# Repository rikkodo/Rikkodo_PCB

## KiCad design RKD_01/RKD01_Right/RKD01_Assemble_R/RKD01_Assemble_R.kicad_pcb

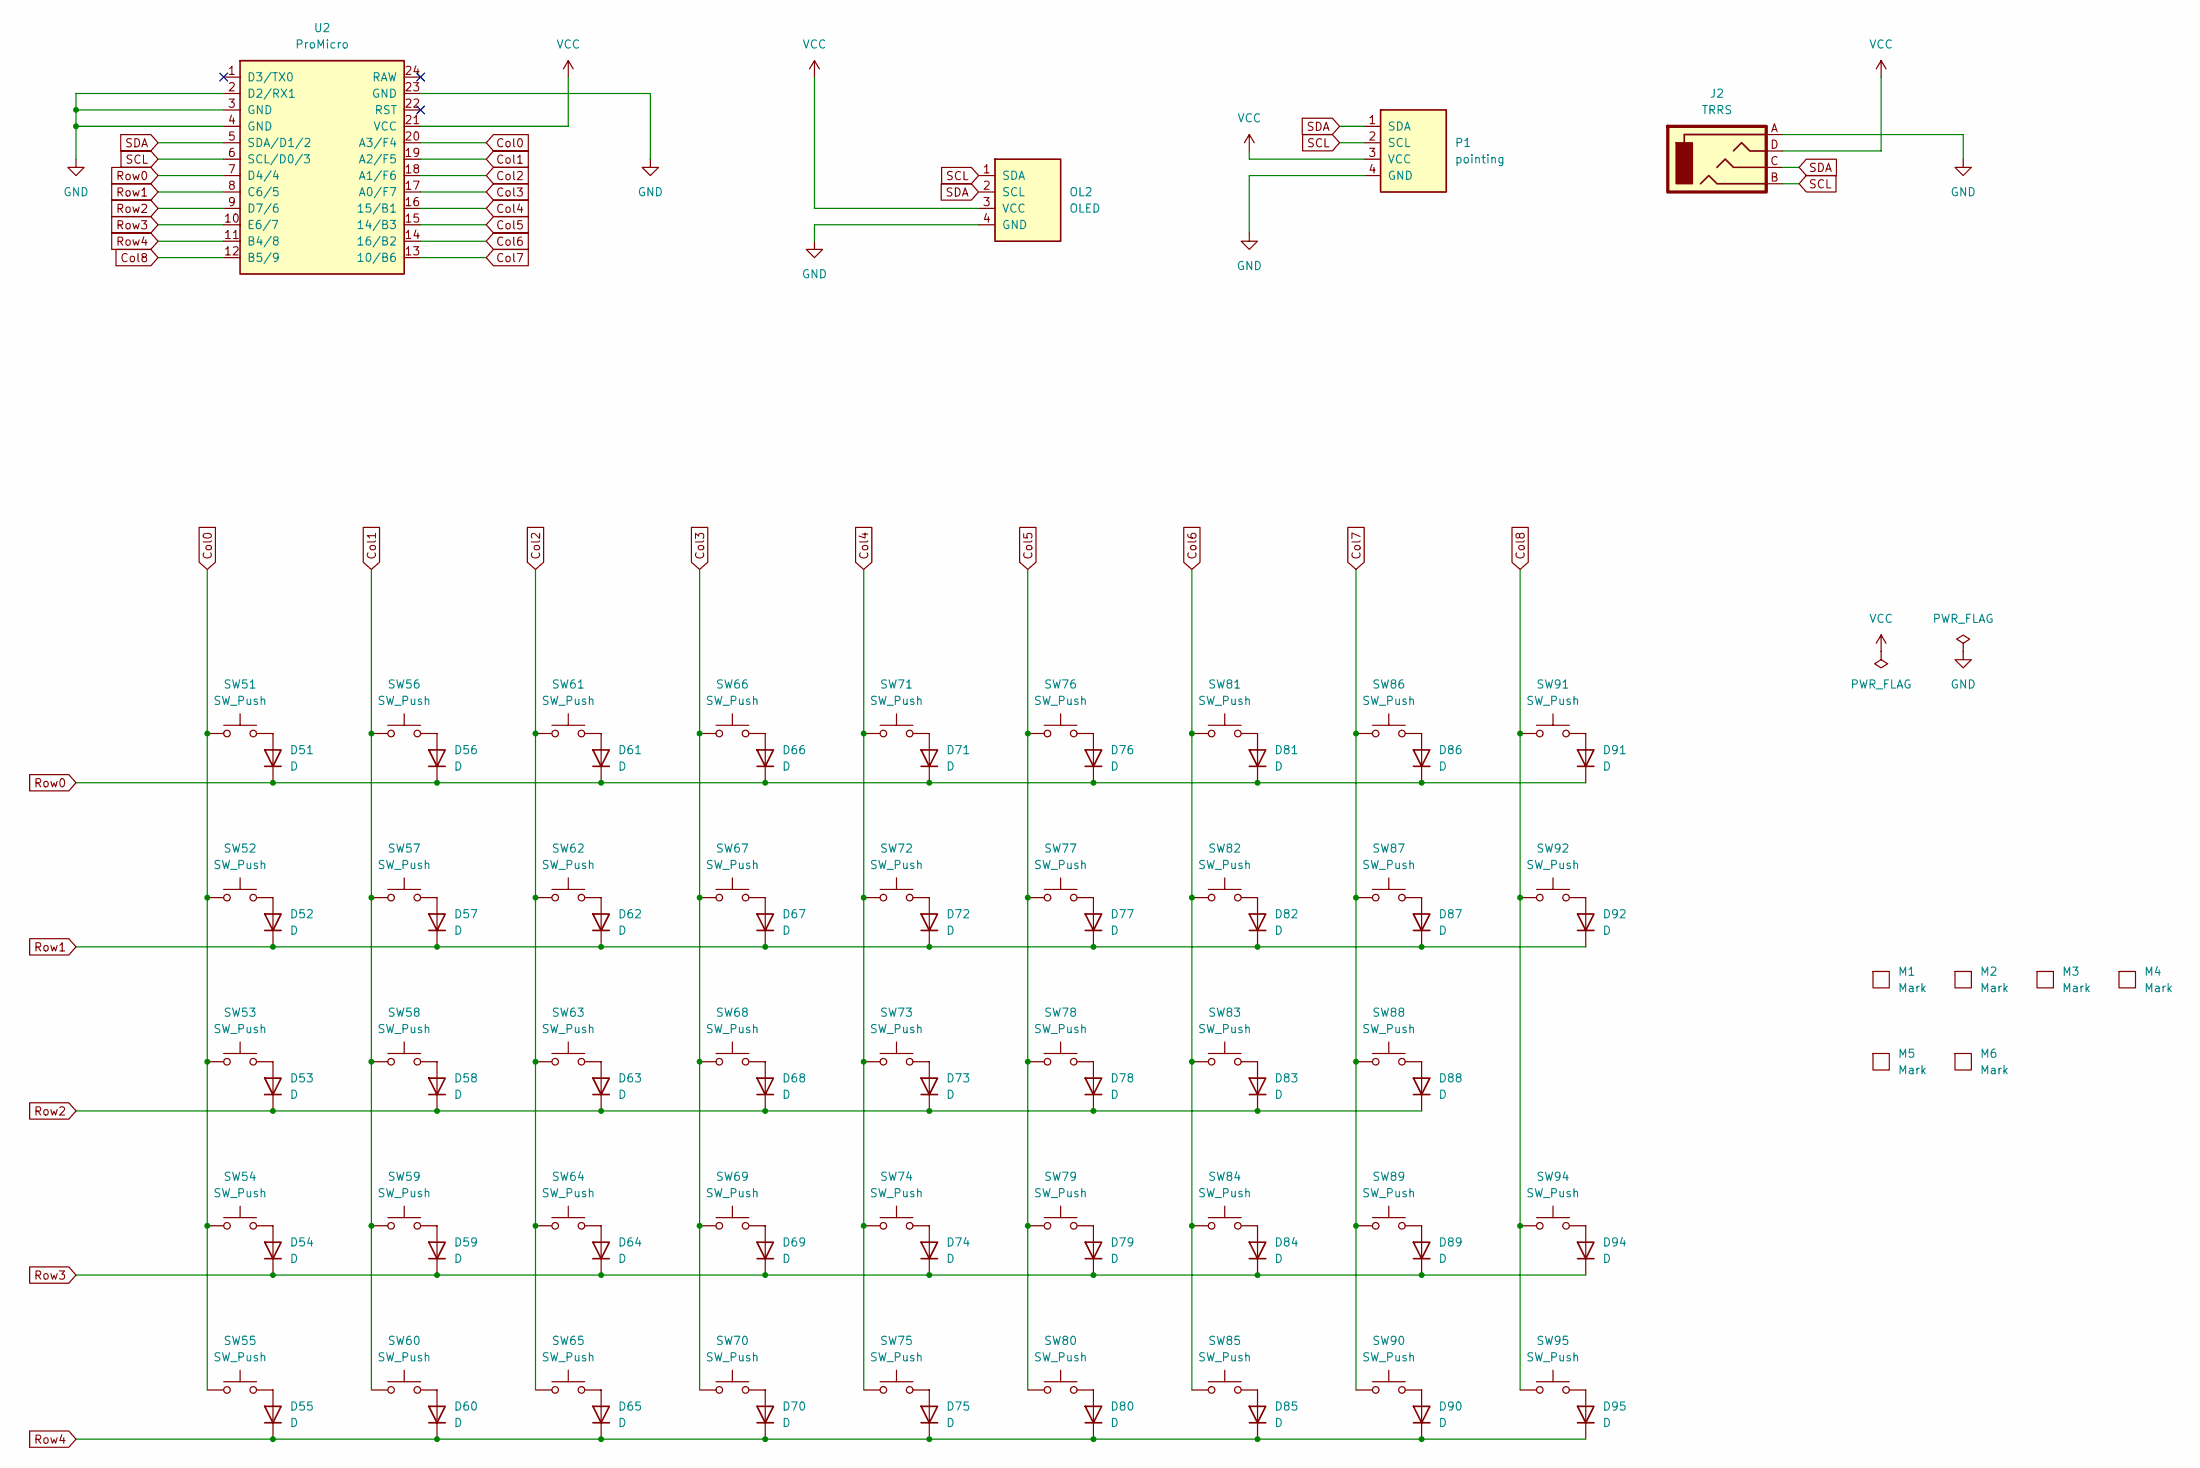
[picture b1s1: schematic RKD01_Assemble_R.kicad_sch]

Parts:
D51, D52, D53, D54, D55, D56, D57, D58, D59, D60, D61, D62, D63, D64, D65, D66, D67, D68, D69, D70, D71, D72, D73, D74, D75, D76, D77, D78, D79, D80, D81, D82, D83, D84, D85, D86, D87, D88, D89, D90, D91, D92, D94, D95: D; Diode_TH_SMD
J2: TRRS; TRRS_PJ-320A
M1, M2, M3, M4: Mark; m2_Spacer_Hole_hex
M5, M6: Mark; m2_Screw_Hole
OL2: OLED; OLED_center_module
P1: pointing; OLED
SW51, SW52, SW53, SW54, SW55, SW56, SW57, SW58, SW59, SW60, SW61, SW62, SW63, SW64, SW65, SW66, SW67, SW68, SW69, SW70, SW71, SW72, SW73, SW74, SW75, SW76, SW77, SW78, SW79, SW80, SW81, SW82, SW83, SW84, SW85, SW86, SW87, SW89, SW90, SW92, SW94, SW95: SW_Push; rkd_Choc_v2_Hotswap_1u
SW88, SW91: SW_Push; rkd_Choc_v2_Hotswap_2u
U2: ProMicro; ProMicro_r

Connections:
Col0: SW51.2, SW52.2, SW53.2, SW54.2, SW55.2, U2.20 (A3/F4)
Col1: SW56.2, SW57.2, SW58.2, SW59.2, SW60.2, U2.19 (A2/F5)
Col2: SW61.2, SW62.2, SW63.2, SW64.2, SW65.2, U2.18 (A1/F6)
Col3: SW66.2, SW67.2, SW68.2, SW69.2, SW70.2, U2.17 (A0/F7)
Col4: SW71.2, SW72.2, SW73.2, SW74.2, SW75.2, U2.16 (15/B1)
Col5: SW76.2, SW77.2, SW78.2, SW79.2, SW80.2, U2.15 (14/B3)
Col6: SW81.2, SW82.2, SW83.2, SW84.2, SW85.2, U2.14 (16/B2)
Col7: SW86.2, SW87.2, SW88.2, SW89.2, SW90.2, U2.13 (10/B6)
Col8: SW91.2, SW92.2, SW94.2, SW95.2, U2.12 (B5/9)
GND: J2.A, OL2.4 (GND), P1.4 (GND), U2.2 (D2/RX1), U2.3 (GND), U2.4 (GND), U2.23 (GND)
unnamed: D51.2 (A), SW51.1
unnamed: D52.2 (A), SW52.1
unnamed: D53.2 (A), SW53.1
unnamed: D54.2 (A), SW54.1
unnamed: D55.2 (A), SW55.1
unnamed: D56.2 (A), SW56.1
unnamed: D57.2 (A), SW57.1
unnamed: D58.2 (A), SW58.1
unnamed: D59.2 (A), SW59.1
unnamed: D60.2 (A), SW60.1
unnamed: D61.2 (A), SW61.1
unnamed: D62.2 (A), SW62.1
unnamed: D63.2 (A), SW63.1
unnamed: D64.2 (A), SW64.1
unnamed: D65.2 (A), SW65.1
unnamed: D66.2 (A), SW66.1
unnamed: D67.2 (A), SW67.1
unnamed: D68.2 (A), SW68.1
unnamed: D69.2 (A), SW69.1
unnamed: D70.2 (A), SW70.1
unnamed: D71.2 (A), SW71.1
unnamed: D72.2 (A), SW72.1
unnamed: D73.2 (A), SW73.1
unnamed: D74.2 (A), SW74.1
unnamed: D75.2 (A), SW75.1
unnamed: D76.2 (A), SW76.1
unnamed: D77.2 (A), SW77.1
unnamed: D78.2 (A), SW78.1
unnamed: D79.2 (A), SW79.1
unnamed: D80.2 (A), SW80.1
unnamed: D81.2 (A), SW81.1
unnamed: D82.2 (A), SW82.1
unnamed: D83.2 (A), SW83.1
unnamed: D84.2 (A), SW84.1
unnamed: D85.2 (A), SW85.1
unnamed: D86.2 (A), SW86.1
unnamed: D87.2 (A), SW87.1
unnamed: D88.2 (A), SW88.1
unnamed: D89.2 (A), SW89.1
unnamed: D90.2 (A), SW90.1
unnamed: D91.2 (A), SW91.1
unnamed: D92.2 (A), SW92.1
unnamed: D94.2 (A), SW94.1
unnamed: D95.2 (A), SW95.1
Row0: D51.1 (K), D56.1 (K), D61.1 (K), D66.1 (K), D71.1 (K), D76.1 (K), D81.1 (K), D86.1 (K), D91.1 (K), U2.7 (D4/4)
Row1: D52.1 (K), D57.1 (K), D62.1 (K), D67.1 (K), D72.1 (K), D77.1 (K), D82.1 (K), D87.1 (K), D92.1 (K), U2.8 (C6/5)
Row2: D53.1 (K), D58.1 (K), D63.1 (K), D68.1 (K), D73.1 (K), D78.1 (K), D83.1 (K), D88.1 (K), U2.9 (D7/6)
Row3: D54.1 (K), D59.1 (K), D64.1 (K), D69.1 (K), D74.1 (K), D79.1 (K), D84.1 (K), D89.1 (K), D94.1 (K), U2.10 (E6/7)
Row4: D55.1 (K), D60.1 (K), D65.1 (K), D70.1 (K), D75.1 (K), D80.1 (K), D85.1 (K), D90.1 (K), D95.1 (K), U2.11 (B4/8)
SCL: J2.B, OL2.1 (SDA), P1.2 (SCL), U2.6 (SCL/D0/3)
SDA: J2.C, OL2.2 (SCL), P1.1 (SDA), U2.5 (SDA/D1/2)
VCC: J2.D, OL2.3 (VCC), P1.3 (VCC), U2.21 (VCC)

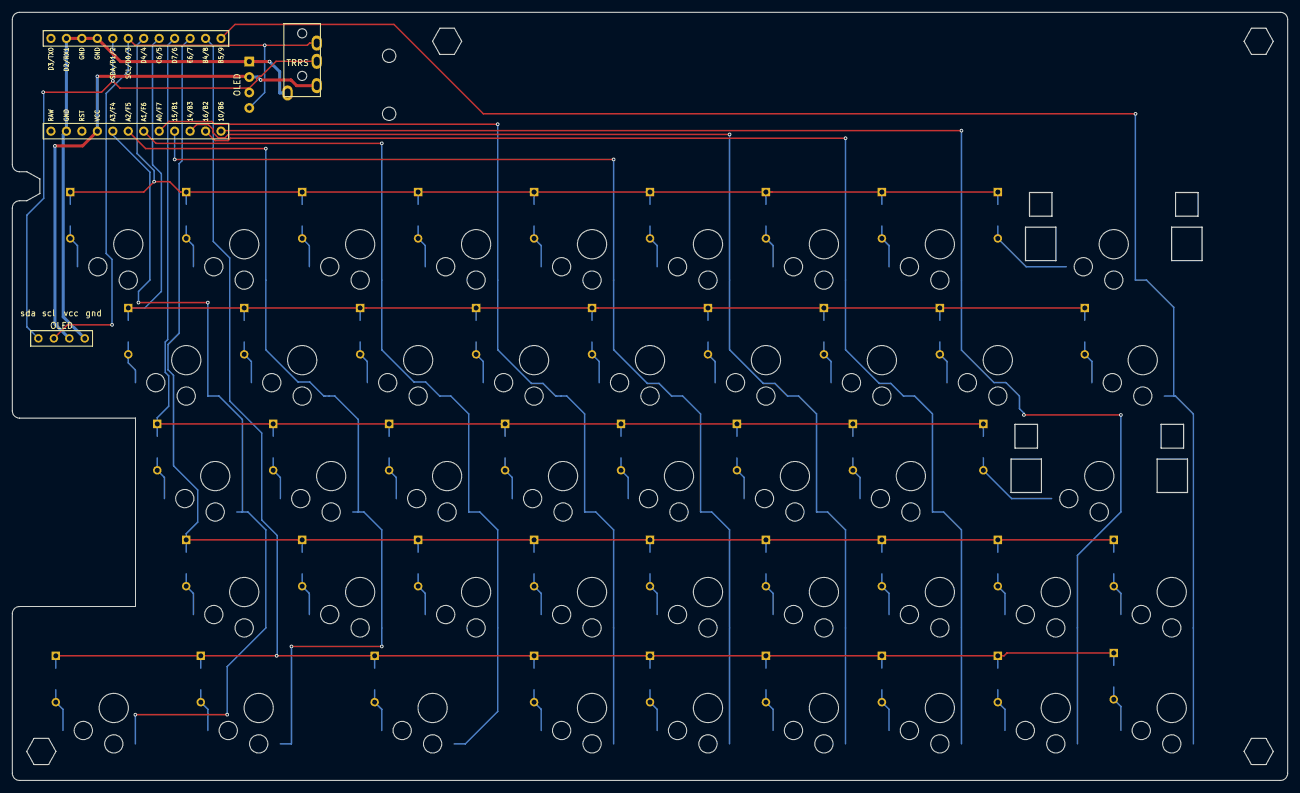
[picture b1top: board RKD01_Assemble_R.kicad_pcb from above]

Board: 2 copper layers, 209.6 x 126.2 mm, 98 parts (0 on the bottom side), 62 nets.
